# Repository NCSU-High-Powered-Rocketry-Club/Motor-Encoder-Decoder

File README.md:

# Motor Encoder Decoder
This project contains the KiCad files for HPRC's Motor Encoder Decoder board. This PCB was designed for the club's rover payload, which will be flown in the 2027 IREC competition.

## Description
The Motor Encoder Decoder is intended to be used with a [Motoron M2T256 Dual I2C Motor Controller](https://www.pololu.com/product/5065) and powers two 12V DC motors using JST connectors. These connectors will connect to [Pololu rotary encoders](https://www.pololu.com/product/5661) that will be mounted on the gear motors for the rover's wheels. Encoder position is received through these connectors in the form of quadrature square waves and counted with the LS7866C quadrature counter. This data is retrieved off the board using the same i2c bus that controls the motors.

## Component Overview
The [LS7866C](https://lsicsi.com/wp-content/uploads/2025/05/LS7866C.pdf) is the primary component of this board, allowing the quadrature encoder data to be connected directly and counted, up to 32 bits. The primary motivation for this was to free up GPIO's and computation time from the Raspberry Pi, as well as being more robust instead of relying on the Pi's OS catching every clock edge.

A board-mount Wago is used for easy connection of the main power, and reliability for the high-current connection. The board was designed with 1.8A peak current per motor in mind, and the Wago is more than capable of handling this. We are supplying 12V to the Wago to power the motors on the rover.

The board is powered using 3.3V to power the LS7866C, and must use 3.3V logic-level I2C.

## PCBWay
A special thank you to our sponsor, [PCBWay](https://www.pcbway.com/), for supporting the manufacturing of this custom PCB! As a competitive high-powered rocketry team, reliable electronics are essential to the success of our projects. PCBWay's high-quality PCB manufacturing services have helped us turn our designs into functional hardware, allowing us to develop and test custom electronics for our rockets and payloads. Their support, attention to detail, and excellent communication throughout the manufacturing process have been greatly appreciated. We are grateful for their contribution to our team's success and highly recommend checking out their services for your next electronics project!

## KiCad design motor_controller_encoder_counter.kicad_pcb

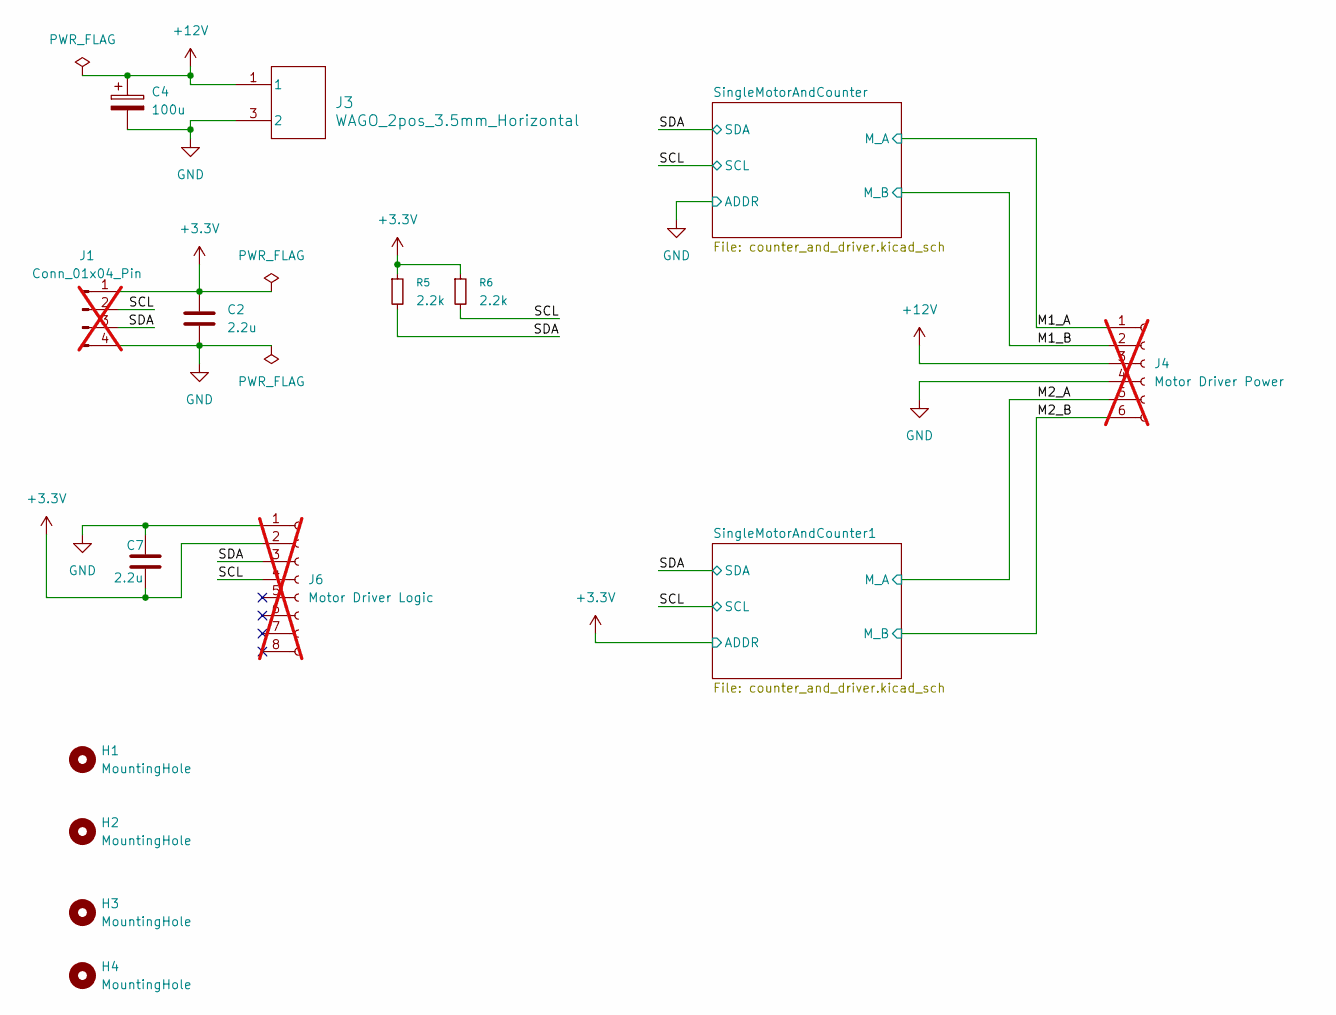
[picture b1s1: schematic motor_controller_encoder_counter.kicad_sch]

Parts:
C2, C7: 2.2u; C_0402_1005Metric; Manufacturer PN GRM155R61C225KE44D
C4: 100u; CP_Elec_5x5.8; Manufacturer PN APXG160ARA101ME61G
H1, H2, H3, H4: MountingHole; MountingHole_2.2mm_M2
J1: Conn_01x04_Pin; PinHeader_1x04_P2.54mm_Vertical; not fitted
J3: WAGO_2pos_3.5mm_Horizontal; Manufacturer PN 2601-1102
J4: Motor Driver Power; PinSocket_1x06_P2.54mm_Vertical; not fitted
J6: Motor Driver Logic; PinSocket_1x08_P2.54mm_Vertical; not fitted
R5, R6: 2.2k; R_0402_1005Metric; Manufacturer PN RC0402FR-072k2L

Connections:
+3.3V: C2.2, C7.1, J1.1, J6.2, R5.1, R6.1; also elsewhere on the board
+12V: C4.1, J3.1, J3.2 (1_2), J4.3
/M1_A: J4.1; also elsewhere on the board
/M1_B: J4.2; also elsewhere on the board
/M2_A: J4.5; also elsewhere on the board
/M2_B: J4.6; also elsewhere on the board
/SCL: J1.2, J6.4, R6.2; also elsewhere on the board
/SDA: J1.3, J6.3, R5.2; also elsewhere on the board
GND: C2.1, C4.2, C7.2, J1.4, J3.3 (2), J3.4 (2_2), J4.4, J6.1; also elsewhere on the board

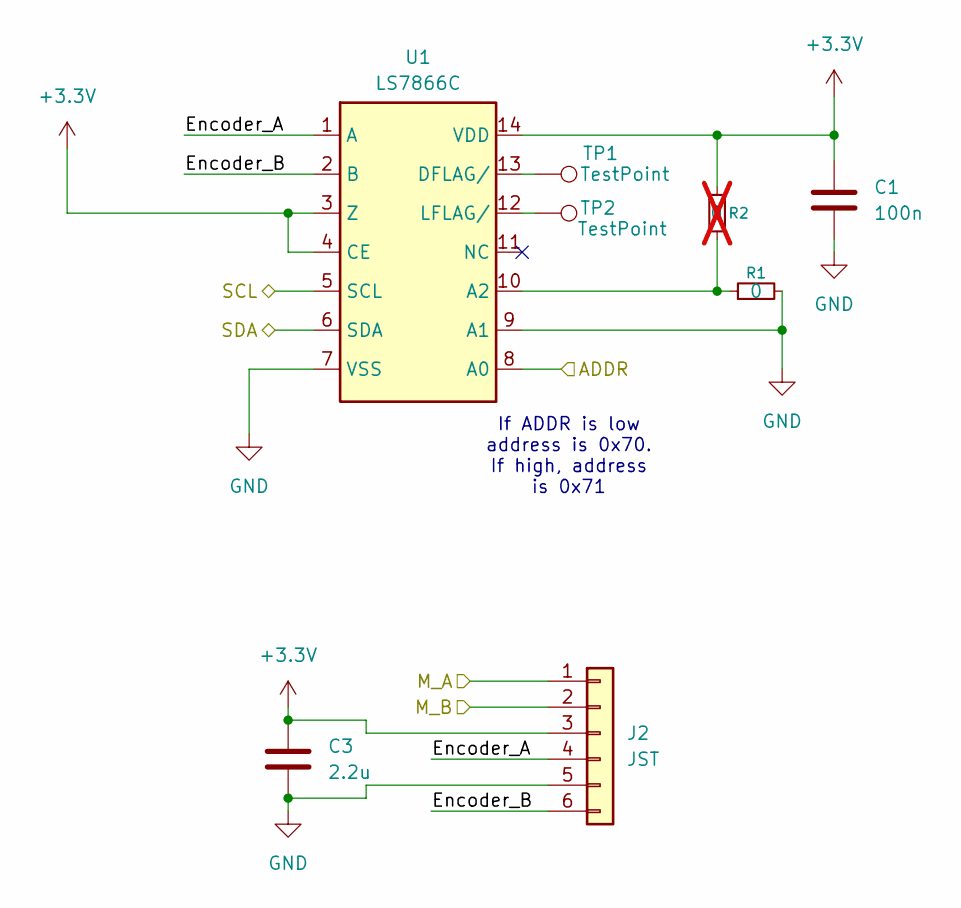
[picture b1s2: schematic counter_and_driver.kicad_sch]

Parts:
C1: 100n; C_0402_1005Metric; Manufacturer PN GCM155R71H104KE02D
C3: 2.2u; C_0402_1005Metric; Manufacturer PN GRM155R61C225KE44D
J2: JST; JST_PH_S6B-PH-K_1x06_P2.00mm_Horizontal; Manufacturer PN S6B-PH-K-S
R1: 0; R_0402_1005Metric; Manufacturer PN RC0402FR-070RL
R2: 0; R_0402_1005Metric; not fitted
TP1, TP2: TestPoint; TestPoint_Pad_1.0x1.0mm
U1: LS7866C; TSSOP-14_4.4x5mm_P0.65mm; Manufacturer PN LS7866C-TS

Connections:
+3.3V: C1.2, C3.1, J2.3, R2.2, U1.3 (Z), U1.4 (CE), U1.14 (VDD); also elsewhere on the board
/M1_A: J2.1; also elsewhere on the board
/M1_B: J2.2; also elsewhere on the board
/SCL: U1.5 (SCL); also elsewhere on the board
/SDA: U1.6 (SDA); also elsewhere on the board
/SingleMotorAndCounter/Encoder_A: J2.4, U1.1 (A)
/SingleMotorAndCounter/Encoder_B: J2.6, U1.2 (B)
GND: C1.1, C3.2, J2.5, R1.2, U1.7 (VSS), U1.8 (A0), U1.9 (A1); also elsewhere on the board
unnamed: R1.1, R2.1, U1.10 (A2)
unnamed: TP1.1 (1_1), U1.13 (DFLAG/)
unnamed: TP2.1 (1_1), U1.12 (LFLAG/)

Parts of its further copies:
C5: 100n; C_0402_1005Metric; Manufacturer PN GCM155R71H104KE02D
C6: 2.2u; C_0402_1005Metric; Manufacturer PN GRM155R61C225KE44D
J8: JST; JST_PH_S6B-PH-K_1x06_P2.00mm_Horizontal; Manufacturer PN S6B-PH-K-S
R3: 0; R_0402_1005Metric; not fitted
R4: 0; R_0402_1005Metric; Manufacturer PN RC0402FR-070RL
TP3, TP4: TestPoint; TestPoint_Pad_1.0x1.0mm
U2: LS7866C; TSSOP-14_4.4x5mm_P0.65mm; Manufacturer PN LS7866C-TS

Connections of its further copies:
+3.3V: C5.2, C6.1, J8.3, R3.2, U2.3 (Z), U2.4 (CE), U2.8 (A0), U2.14 (VDD); also elsewhere on the board
/M2_A: J8.1; also elsewhere on the board
/M2_B: J8.2; also elsewhere on the board
/SCL: U2.5 (SCL); also elsewhere on the board
/SDA: U2.6 (SDA); also elsewhere on the board
/SingleMotorAndCounter1/Encoder_A: J8.4, U2.1 (A)
/SingleMotorAndCounter1/Encoder_B: J8.6, U2.2 (B)
GND: C5.1, C6.2, J8.5, R4.2, U2.7 (VSS), U2.9 (A1); also elsewhere on the board
unnamed: R3.1, R4.1, U2.10 (A2)
unnamed: TP3.1 (1_1), U2.13 (DFLAG/)
unnamed: TP4.1 (1_1), U2.12 (LFLAG/)

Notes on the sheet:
If ADDR is low address is 0x70. If high, address is 0x71

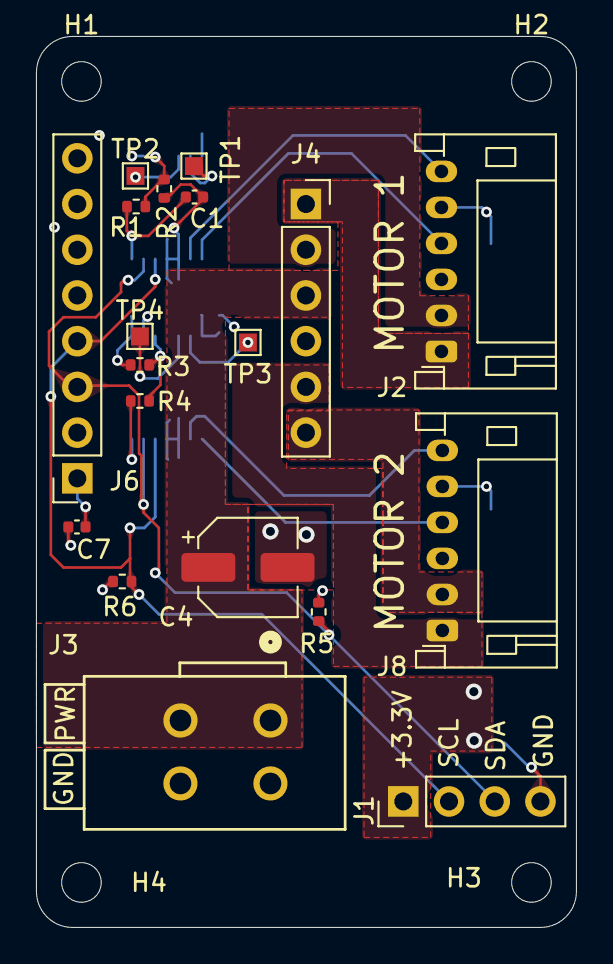
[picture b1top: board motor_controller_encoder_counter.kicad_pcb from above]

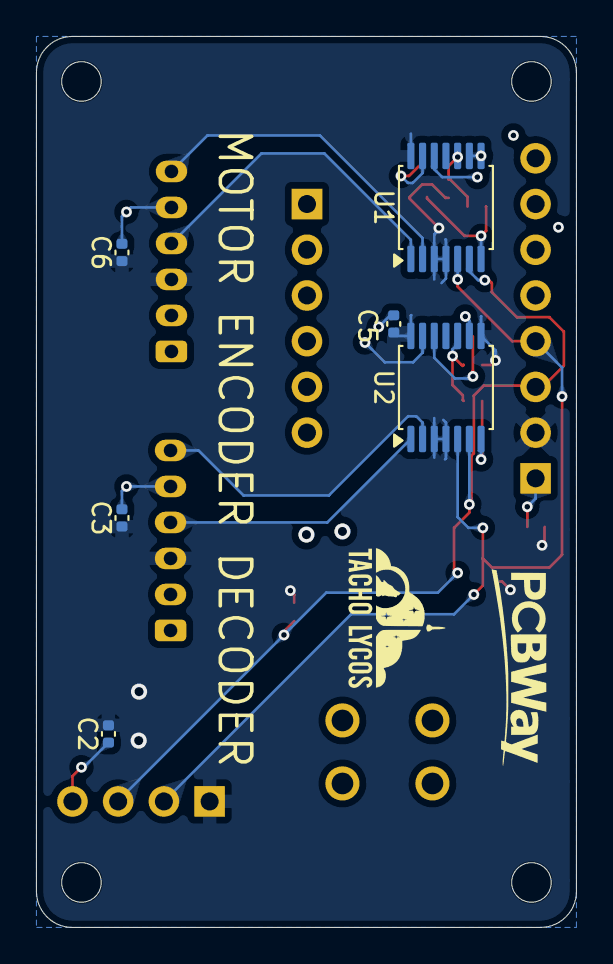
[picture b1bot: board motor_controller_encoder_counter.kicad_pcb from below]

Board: 4 copper layers, 30.0 x 49.5 mm, 29 parts (6 on the bottom side), 19 nets.
